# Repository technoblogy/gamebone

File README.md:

# GameBone
A simple handheld electronic game based on an ATtiny85. For more information see: http://www.technoblogy.com/show?1K2Z.

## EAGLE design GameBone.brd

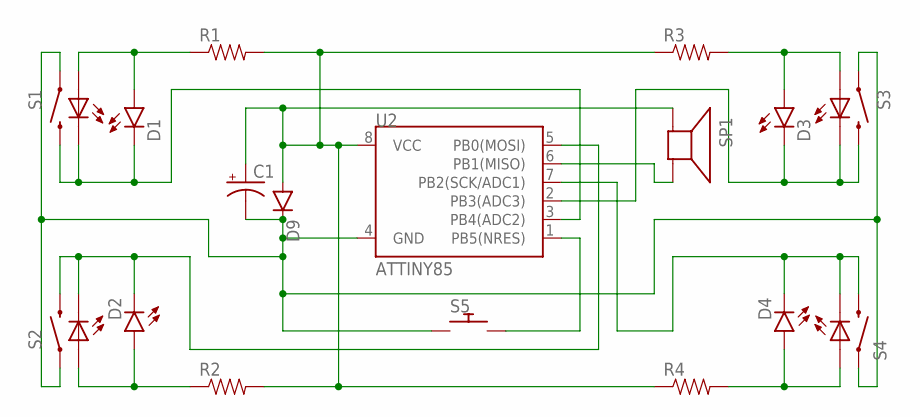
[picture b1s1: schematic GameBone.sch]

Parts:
C1: 10UF-25V-20%(PTH); CPOL-RADIAL-10UF-25V
D1, D2, D3, D4: LED5MM
D9: DIODEPTH; DIODE-1N4001
R1, R2, R3, R4: RESISTORPTH-1/4W; AXIAL-0.4
S1, S2, S3, S4: SWITCH-MOMENTARY-LEDPTH; TACTILE-PTH-LED-12MM
S5: SWITCH_PUSHBUTTONEVQ-PE; TACT_PANA-EVQ
SP1: SPEAKER/AL60P; AL60P
U2: ATTINY85; DIP08

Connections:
unnamed: C1.1 (+), D9.A, R1.P$2 (2), R2.P$2 (2), R3.P$1 (1), R4.P$1 (1), SP1.1 (+), U2.8 (VCC)
unnamed: C1.2 (-), D9.C, S1.4 (1), S2.4 (1), S3.4 (1), S4.4 (1), S5.P$1, U2.4 (GND)
unnamed: SP1.2 (-), U2.6 (PB1(MISO))
unnamed: D4.K (C), S4.2, S4.C, U2.7 (PB2(SCK/ADC1))
unnamed: S5.P$2, U2.1 (PB5(NRES))
unnamed: D2.K (C), S2.2, S2.C, U2.5 (PB0(MOSI))
unnamed: D1.K (C), S1.2, S1.C, U2.3 (PB4(ADC2))
unnamed: D3.K (C), S3.2, S3.C, U2.2 (PB3(ADC3))
unnamed: D2.A, R2.P$1 (1), S2.A
unnamed: D1.A, R1.P$1 (1), S1.A
unnamed: D3.A, R3.P$2 (2), S3.A
unnamed: D4.A, R4.P$2 (2), S4.A

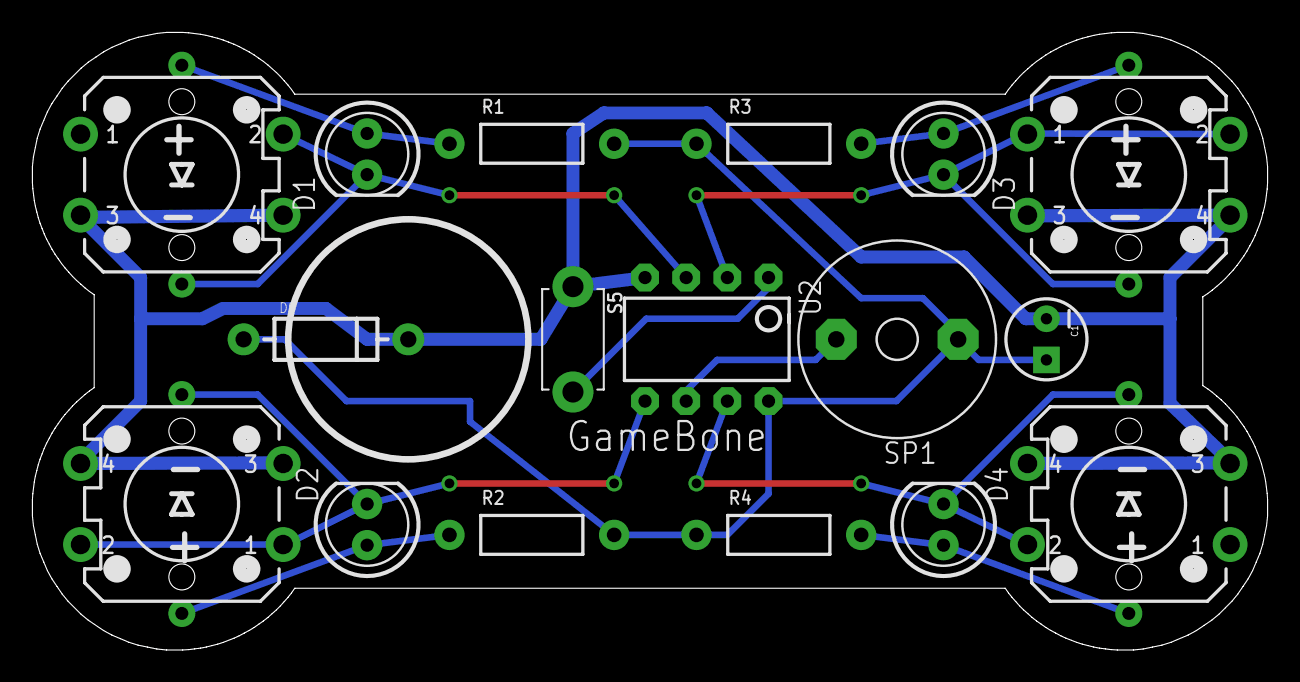
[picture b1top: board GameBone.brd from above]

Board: 2 copper layers, 76.2 x 38.1 mm, 17 parts (0 on the bottom side), 12 nets.

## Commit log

2017-01-23 Latest
2017-01-23 Version 1 - 23rd January 2017
2017-01-23 Version 1 - Eagle files
2020-12-07 Version 2 - 7th December 2020
    Updates the note() routine to leave the output in a high-impedance state when no note is playing, to avoid possible noise from the speaker.

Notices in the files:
parts and their libraries:
SparkFun-LED: Licensing: Creative Commons ShareAlike 4.0 International - https://creativecommons.org/licenses/by-sa/4.0
